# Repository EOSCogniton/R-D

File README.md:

# R-D Repository

Ce repository a été créé à l'occasion des stages d'applications de la Saison 2024, afin de permettre une conservation des connaissances acquises lors de ceux-ci. Il contient à ce jour les connaissances acquises sur la réalisation d'un VCU home-made.
Il est actuellement en cours de construction.

## Table of contents
1. VCU

## VCU
La partie VCU du repository contient le travail réalisé sur le VCU lors du stage FS@ECL de la Saison 2024. Lors de ce stage, un cahier des charges a été du VCU a été effectué ce qui a mené à un choix de micro-contrôleur sur lequel a été basé un banc de test.
Le cahier des charges est disponible directement dans le dossier "VCU", et les informations pertinentes par rapport au banc de test sont dans le dossier "VCU/Banc de test/"

### Banc de test du VCU basé sur le MCU ATSAMC21J18A-ANT
Description des différents documents présents dans le dossier "VCU/Banc de test/". Le travail a principalement été réalisé pour fournir des outils par rapport au test du code du VCU, en réalisant un banc de test à brancher à la carte de développement.

#### Dev_board_connector.png
Schéma des pins de la carte de développement ATSAMC21-XPro pour le MCU ATSAMC21J18.

#### Interface_Pins_Devboard.xlsx
Ce tableur est décomposé en deux feuilles : "PINS correspondance" et "références composants".*

Dans la feuille PINS correspondance, l'utilisation des différents pins utilisable par la carte de développement est détaillé.
Pour chaque pins de la carte, il est indiqué lesquels sont utilisés, à quelle pin du MCU ils sont reliés et à la fonctionnalité choisie pour le pin. Une description plus factuelle est aussi fournie avec des précisions sur l'utilisation du pin.

Dans la feuille "références composants", l'ensemble des composants utilisés pour la réalisation du pcb sont présents (hors résistances, condensateurs et connecteurs qui sont couramment utilisés dans l'écurie. Si besoin il est possible de retrouver les références sur le schematics KiCad). il sera notamment possible de trouver les références des régulateurs de tension linéaires, des LEDs, des potentiomètres, des switchs, des transceiver CAN et de la carte de développement ATSAMC21-XPro.

#### Schematics-banc
Schematics du pcb.

#### Code 
Exemple de code effectué sur MPLab X IDE pour mesurer un ADC.

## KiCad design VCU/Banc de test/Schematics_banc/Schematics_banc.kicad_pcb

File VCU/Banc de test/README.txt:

Banc de test du VCU ATSAMC21J18A-ANT

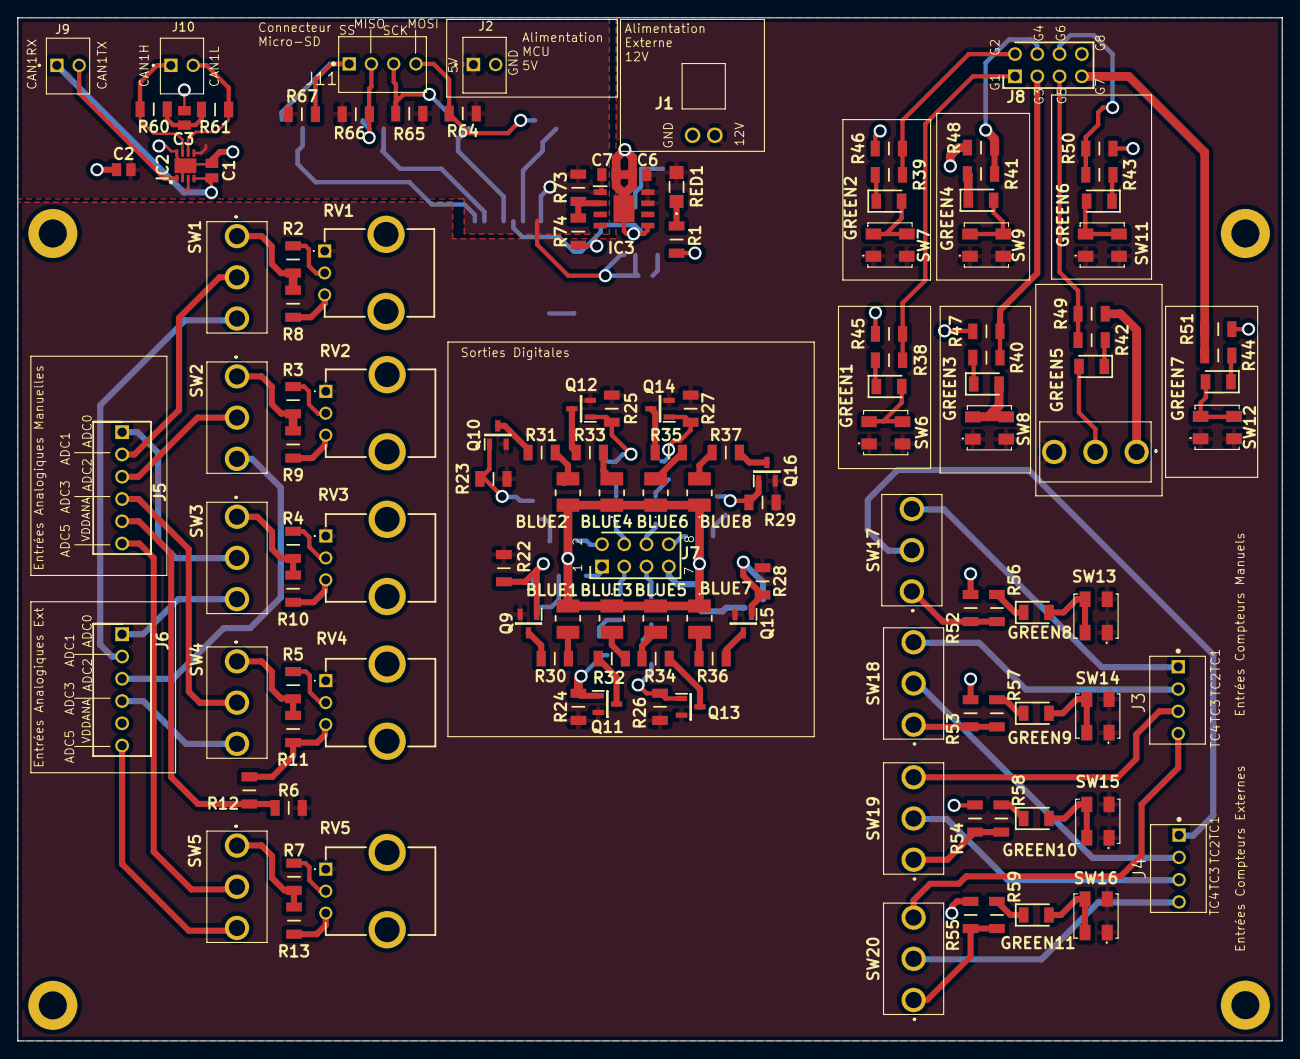
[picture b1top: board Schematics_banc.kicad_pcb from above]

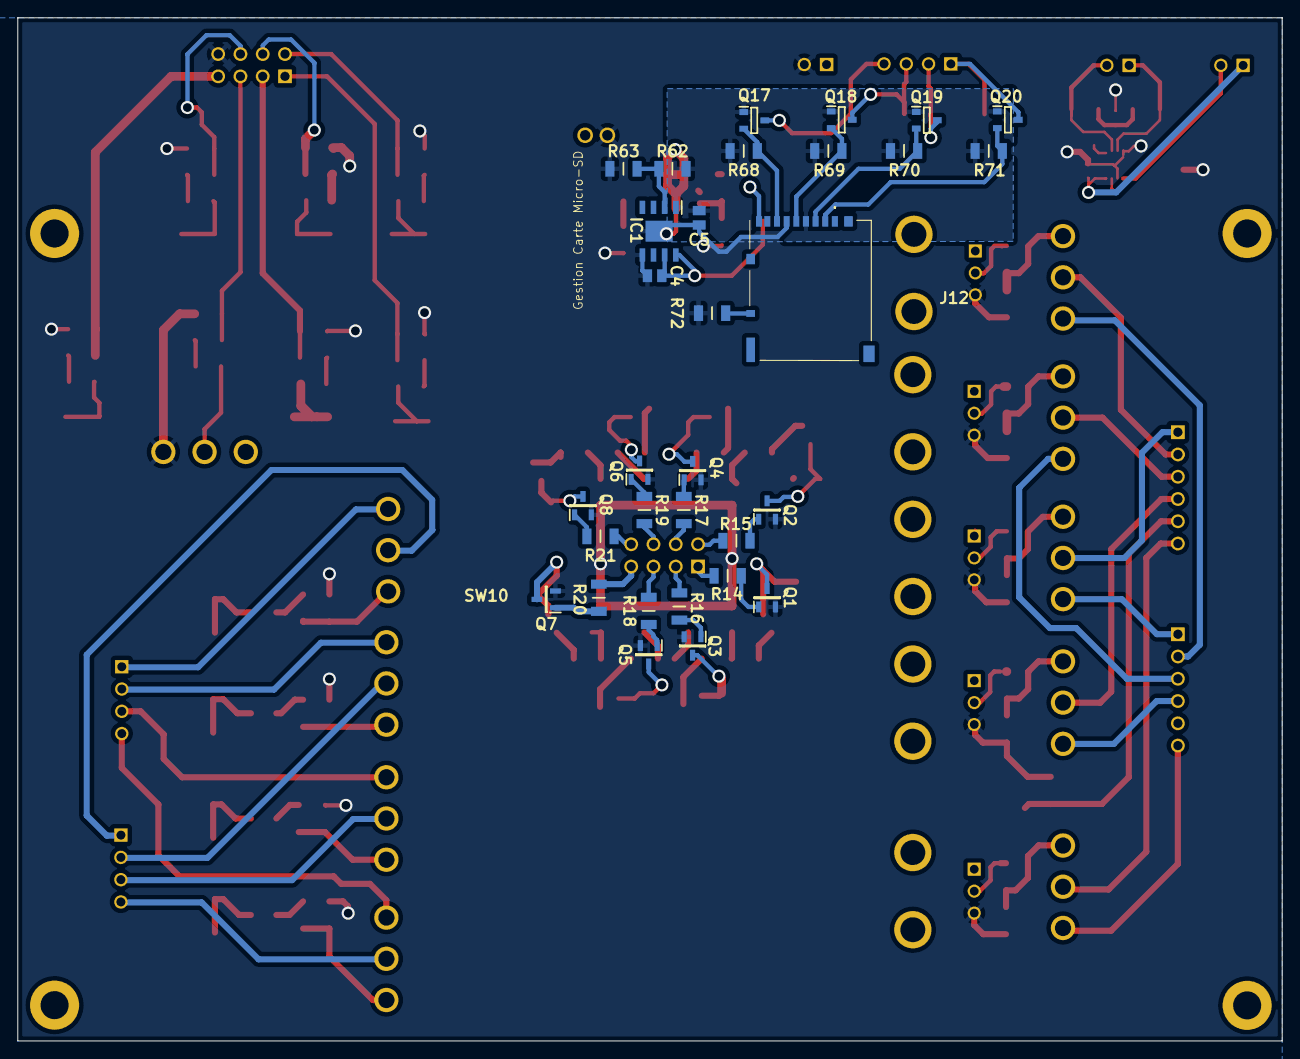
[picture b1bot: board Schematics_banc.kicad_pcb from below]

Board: 2 copper layers, 144.2 x 116.7 mm, 165 parts (31 on the bottom side), 123 nets.

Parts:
BLUE1, BLUE2, BLUE3, BLUE4, BLUE5, BLUE6, BLUE7, BLUE8: LB_T64G-V2CA-59-Z484; LBT64GV2CA59Z484
C1: 15p; CAPC2012X130N
C2: 100n; CAPC2012X130N
C3: 4.7u; CAPC2012X130N
C4, C7: 1u; CAPC2012X130N
C5, C6: 2.2u; CAPC2012X130N
GREEN1, GREEN2, GREEN3, GREEN4, GREEN5, GREEN6, GREEN7, GREEN8, GREEN9, GREEN10, GREEN11: VFJD1105W-5C63A-TR; LEDC3216X195N
IC1, IC3: TPS7B8633QDDARQ1; SOIC127P600X170-9N
IC2: ATA6561-GBQW-N; SON65P300X300X90-9N-D
J1: 2P Angle 171857-4002; 1718574002
J2, J9, J10: 2P Droit 2-11-2022; MOLEX_22-11-2022
J3, J4, J11: 4P Droit 22-11-2042; MOLEX_22-11-2042
J5, J6: 6P Droit 22-11-2062; HDRV6W87P0X254_1X6_1509X635X1092P
J7, J8: 10-97-7086; HDRV8W87P254_2X4_1016X508X1055P
J12: DM3AT-SF-PEJM5_40_; DM3ATSFPEJM540
M2, M2#2, M2#3, M2#4: MountingHole_3.2mm_M3_DIN965_Pad
Q1, Q2, Q3, Q4, Q5, Q6, Q7, Q8: MMBF170; SOT96P237X111-3N
Q9, Q10, Q11, Q12, Q13, Q14, Q15, Q16: SI2337DS-T1-BE3; SOT95P237X112-3N
Q17, Q18, Q19, Q20: BSS138; SOT95P240X120-3N
R1, R2, R3, R4, R5, R6, R7, R38, R39, R40, R41, R42, R43, R44, R52, R53, R54, R55: 21.5k; RESC3216X70N
R8, R9, R10, R11, R12, R13, R45, R46, R47, R48, R49, R50, R51, R56, R57, R58, R59: 11k; RESC3216X70N
R14, R15, R16, R17, R18, R19, R20, R21: 600; RESC3216X70N
R22, R23, R24, R25, R26, R27, R28, R29, R30, R31, R32, R33, R34, R35, R36, R37: 3k; RESC3216X70N
R60, R61, R72: 4.7k; RESC3216X70N
R62: 4k; RESC3216X70N
R63: 1k; RESC3216X70N
R64, R66, R67, R68, R70, R71: 20k; RESC3216X70N
R65, R69: 10k; RESC3216X70N
R73: 13.3k; RESC3216X70N
R74: 2k; RESC3216X70N
RED1: HSMC-C380; HSMCC380
RV1, RV2, RV3, RV4, RV5: R_Potentiometer; PTV09A4015UA503
SW1, SW2, SW3, SW4, SW5, SW10, SW17, SW18, SW19, SW20: 100SP1T1B4M2QE
SW6, SW7, SW8, SW9, SW11, SW12, SW13, SW14, SW15, SW16: 7914J-1-000E; 7914J1000E

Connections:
5V: C2.2, C4.2, C7.2, IC1.7 (EN), IC1.8 (IN), IC2.3 (VCC), IC2.5 (VIO), IC3.1 (OUT), J2.1, J12.CD1 (CARD_DETECT), R64.2, R65.2, R66.2, R67.2, R73.1
12V: C6.2, IC3.7 (EN), IC3.8 (IN), J1.1, Q9.2 (S), Q10.2 (S), Q11.2 (S), Q12.2 (S), Q13.2 (S), Q14.2 (S), Q15.2 (S), Q16.2 (S), R6.2, R22.1, R23.1, R24.1, R25.1, R26.1, R27.1, R28.1, R29.1, RED1.2 (A), RV1.1, RV2.1, RV3.1, RV4.1, RV5.1, SW6.1, SW6.2, SW7.1, SW7.2, SW8.1, SW8.2, SW9.1, SW9.2, SW10.3 (A), SW11.1, SW11.2, SW12.1, SW12.2, SW13.1, SW13.2, SW14.1, SW14.2, SW15.1, SW15.2, SW16.1, SW16.2
/Conversion 5V-3.3V/3.3V: C5.2, IC1.1 (OUT), J12.4 (VDD), Q17.1 (G), Q18.1 (G), Q19.1 (G), Q20.1 (G), R62.2, R68.2, R69.2, R70.2, R71.2
/Conversion 5V-3.3V/MISO_3.3V: J12.3 (CMD), Q19.2 (S), R70.1
/Conversion 5V-3.3V/MOSI_3.3V: J12.7 (DAT0), Q17.2 (S), R68.1
/Conversion 5V-3.3V/SCK_3.3V: J12.5 (CLK), Q18.2 (S), R69.1
/Conversion 5V-3.3V/SS_3.3V: J12.2 (CD/DAT3), Q20.2 (S), R71.1
ADC5: J5.6, SW5.2 (B)
ADC5_EXT: J6.6, SW5.3 (A)
AIR+_cmd: J7.1, R14.1
AIR+_st: J8.1, R38.1, R45.2
AIR-_cmd: J7.2, R15.1
AIR-_st: J8.2, R39.1, R46.2
APPS1: J5.2, SW1.2 (B)
APPS1_EXT: J6.2, SW1.3 (A)
APPS2: J5.3, SW2.2 (B)
APPS2_EXT: J6.3, SW2.3 (A)
BrakeLight_cmd: J7.3, R16.1
BuzzerR2D_cmd: J7.4, R17.1
CAN1H: IC2.7 (CANH), J10.1, R60.2
CAN1L: IC2.6 (CANL), J10.2, R61.1
CAN1RX: C1.2, IC2.4 (RXD), J9.1
CAN1TX: IC2.1 (TXD), J9.2
Decharge_cmd: J7.6, R19.1
Dry/WetSwitch_st: J8.5, R42.2, R49.2
FBPS: J5.1, SW3.2 (B)
FBPS_EXT: J6.1, SW3.3 (A)
FLWSS_in: J4.2, SW18.2 (B)
FLWSS_out: J3.2, SW18.3 (A)
FRWSS_in: J4.1, SW17.2 (B)
FRWSS_out: J3.1, SW17.3 (A)
GND: BLUE1.1 (K), BLUE2.1 (K), BLUE3.1 (K), BLUE4.1 (K), BLUE5.1 (K), BLUE6.1 (K), BLUE7.1 (K), BLUE8.1 (K), C1.1, C2.1, C3.1, C4.1, C5.1, C6.1, C7.1, IC1.5 (GND_1), IC1.9 (GND_2), IC2.2 (GND), IC2.8 (STBY), IC2.9 (EP), IC3.5 (GND_1), IC3.9 (GND_2), J1.2, J2.2, J8.8, J12.6 (VSS), Q1.2 (S), Q2.2 (S), Q3.2 (S), Q4.2 (S), Q5.2 (S), Q6.2 (S), Q7.2 (S), Q8.2 (S), R1.1, R8.2, R9.2, R10.2, R11.2, R12.2, R13.2, R45.1, R46.1, R47.1, R48.1, R49.1, R50.1, R51.1, R56.1, R57.1, R58.1, R59.1, R63.2, R72.2, R74.2, RV1.3, RV2.3, RV3.3, RV4.3, RV5.3, SW10.1 (C)
GPIO1: J7.7, R20.1
GPIO2: J8.6, R43.1, R50.2
GPIO3: J7.8, R21.1
GPIO4: J8.7, R44.1, R51.2
LV_BATT: J5.5, R6.1, R12.1
MISO_5V: J11.2, Q19.3 (D), R66.1
MOSI_5V: J11.4, Q17.3 (D), R64.1
unnamed: BLUE1.2 (A), R30.2
unnamed: BLUE2.2 (A), R31.2
unnamed: BLUE3.2 (A), R32.2
unnamed: BLUE4.2 (A), R33.2
unnamed: BLUE5.2 (A), R34.2
unnamed: BLUE6.2 (A), R35.2
unnamed: BLUE7.2 (A), R36.2
unnamed: BLUE8.2 (A), R37.2
unnamed: C3.2, R60.1, R61.2
unnamed: GREEN1.2 (A), SW6.3 (K), SW6.4 (A)
unnamed: GREEN1.1 (K), R38.2
unnamed: GREEN2.2 (A), SW7.3 (K), SW7.4 (A)
unnamed: GREEN2.1 (K), R39.2
unnamed: GREEN3.2 (A), SW8.3 (K), SW8.4 (A)
unnamed: GREEN3.1 (K), R40.2
unnamed: GREEN4.2 (A), SW9.3 (K), SW9.4 (A)
unnamed: GREEN4.1 (K), R41.2
unnamed: GREEN5.2 (A), SW10.2 (B)
unnamed: GREEN5.1 (K), R42.1
unnamed: GREEN6.2 (A), SW11.3 (K), SW11.4 (A)
unnamed: GREEN6.1 (K), R43.2
unnamed: GREEN7.2 (A), SW12.3 (K), SW12.4 (A)
unnamed: GREEN7.1 (K), R44.2
unnamed: GREEN8.2 (A), SW13.3 (K), SW13.4 (A)
unnamed: GREEN8.1 (K), R52.2
unnamed: GREEN9.2 (A), SW14.3 (K), SW14.4 (A)
unnamed: GREEN9.1 (K), R53.2
unnamed: GREEN10.2 (A), SW15.3 (K), SW15.4 (A)
unnamed: GREEN10.1 (K), R54.2
unnamed: GREEN11.2 (A), SW16.3 (K), SW16.4 (A)
unnamed: GREEN11.1 (K), R55.2
unnamed: IC1.2 (FB/NC), R62.1, R63.1
unnamed: IC3.2 (FB/NC), R73.2, R74.1
unnamed: Q1.3 (D), Q9.1 (G), R22.2
unnamed: Q1.1 (G), R14.2
unnamed: Q2.1 (G), R15.2
unnamed: Q3.1 (G), R16.2
unnamed: Q4.1 (G), R17.2
unnamed: Q5.1 (G), R18.2
unnamed: Q6.1 (G), R19.2
unnamed: Q7.1 (G), R20.2
unnamed: Q8.1 (G), R21.2
unnamed: Q9.3 (D), R30.1
unnamed: Q10.3 (D), R31.1
unnamed: Q2.3 (D), Q10.1 (G), R23.2
unnamed: Q11.3 (D), R32.1
unnamed: Q3.3 (D), Q11.1 (G), R24.2
unnamed: Q12.3 (D), R33.1
unnamed: Q4.3 (D), Q12.1 (G), R25.2
unnamed: Q13.3 (D), R34.1
unnamed: Q5.3 (D), Q13.1 (G), R26.2
unnamed: Q14.3 (D), R35.1
unnamed: Q6.3 (D), Q14.1 (G), R27.2
unnamed: Q15.3 (D), R36.1
unnamed: Q7.3 (D), Q15.1 (G), R28.2
unnamed: Q16.3 (D), R37.1
unnamed: Q8.3 (D), Q16.1 (G), R29.2
unnamed: R2.2, RV1.2
unnamed: R3.2, RV2.2
unnamed: R4.2, RV3.2
unnamed: R5.2, RV4.2
unnamed: R7.2, RV5.2
unnamed: R1.2, RED1.1 (K)
unnamed: R2.1, R8.1, SW1.1 (C)
unnamed: R3.1, R9.1, SW2.1 (C)
unnamed: R4.1, R10.1, SW3.1 (C)
unnamed: R5.1, R11.1, SW4.1 (C)
unnamed: R7.1, R13.1, SW5.1 (C)
unnamed: R52.1, R56.2, SW17.1 (C)
unnamed: R53.1, R57.2, SW18.1 (C)
unnamed: R54.1, R58.2, SW19.1 (C)
unnamed: R55.1, R59.2, SW20.1 (C)
Precharge_cmd: J7.5, R18.1
R2D_Button: J8.4, R41.1, R48.2
RBPS: J5.4, SW4.2 (B)
RBPS_EXT: J6.4, SW4.3 (A)
RLWSS_in: J4.4, SW20.2 (B)
RLWSS_out: J3.4, SW20.3 (A)
RRWSS_in: J4.3, SW19.2 (B)
RRWSS_out: J3.3, SW19.3 (A)
SCK_5V: J11.3, Q18.3 (D), R65.1
SD_INSERT: J12.MP3, R72.1
SS_SDC_5V: J11.1, Q20.3 (D), R67.1
TSON_Button: J8.3, R40.1, R47.2

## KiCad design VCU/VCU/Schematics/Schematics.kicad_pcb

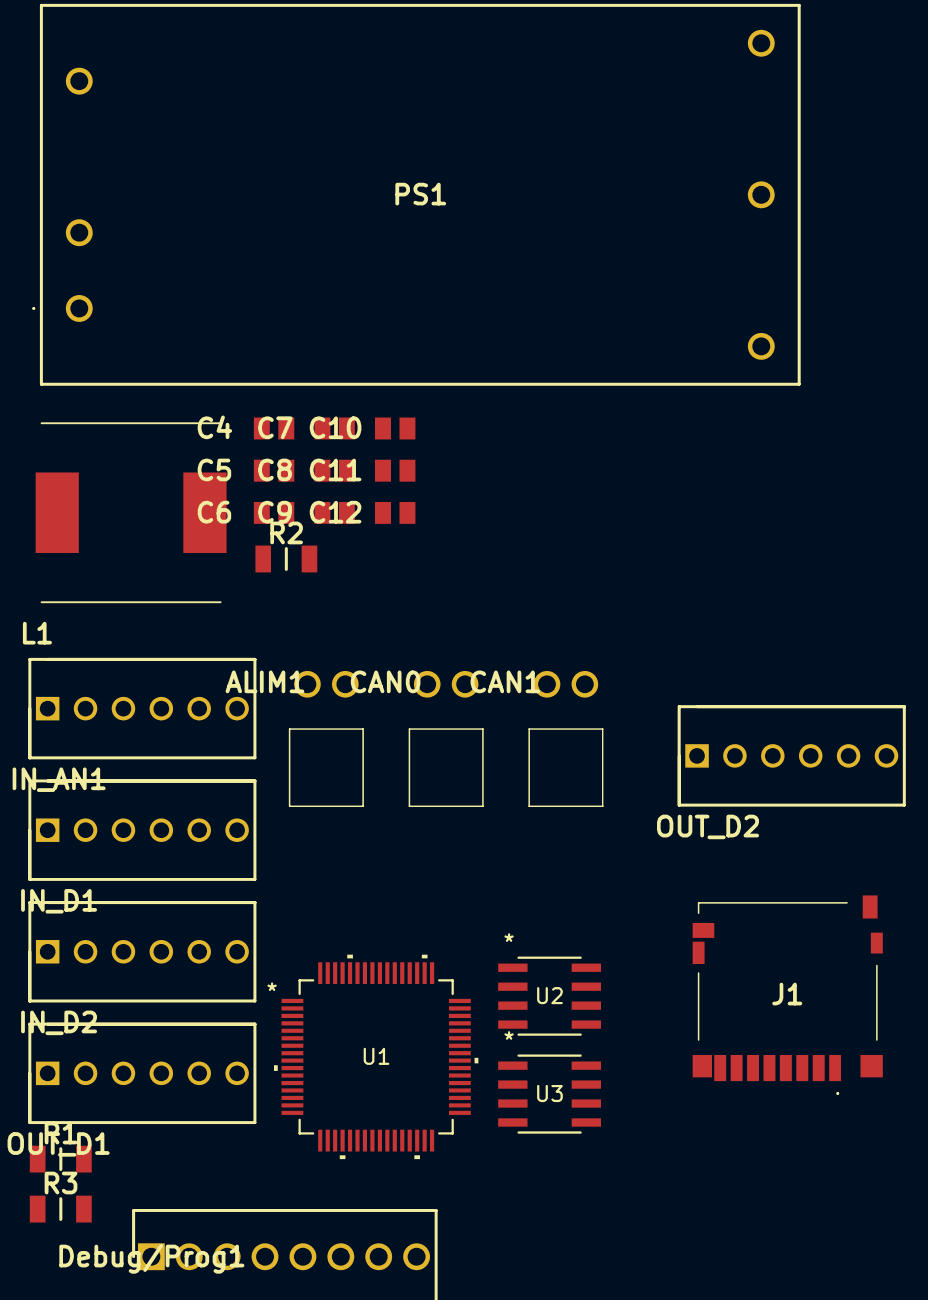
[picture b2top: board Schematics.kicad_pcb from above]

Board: 2 copper layers, 27 parts (0 on the bottom side), 16 nets, no tracks yet.

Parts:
ALIM1: 2P Angle 171857-4002; 1718574002
C4, C6, C7, C9, C12: 100n; CAPC2012X130N
C5, C8: 10u; CAPC2012X130N
C10: 1u; CAPC2012X130N
C11: 22u; CAPC2012X130N
CAN0, CAN1: 2P Angle 171857-4002; 1718574002
Debug/Prog1: 171856-1008; SHDR8W99P0X254_1X8_2017X635X1124P
IN_AN1: 6P Droit 22-11-2062; HDRV6W87P0X254_1X6_1509X635X1092P
IN_D1, IN_D2: 6P Droit 22-11-2062; HDRV6W87P0X254_1X6_1509X635X1092P
J1: DM3D-SF; DM3DSF
L1: 10u; WE-PD_1260_1245_1280_121054
OUT_D1, OUT_D2: 6P Droit 22-11-2062; HDRV6W87P0X254_1X6_1509X635X1092P
PS1: TEN_40-1211E; TEN401211E
R1, R3: 120; RESC3216X70N
R2: 20k; RESC3216X70N
U1: ATSAMC21J18A-ANT; TQFP64_10x10MC_MCH
U2, U3: ATA6561-GAQW-N; SOIC8_4P9X3P9MC_MCH

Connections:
CAN0_H: CAN0.1, R1.2, U2.7 (CANH)
CAN0_L: CAN0.2, R1.1, U2.6 (CANL)
CAN1_H: CAN1.1, R3.2, U3.7 (CANH)
CAN1_L: CAN1.2, R3.1, U3.6 (CANL)
GND: ALIM1.2, C4.1, C5.1, C6.1, C7.1, C8.1, C9.1, C10.1, C11.1, C12.1, Debug/Prog1.3, PS1.2 (-VIN_(GND)), U1.7 (GNDANA), U1.22 (GND), U1.33 (GND), U1.47 (GND), U1.54 (GND), U2.2 (GND), U3.2 (GND)
LV_ALIM: ALIM1.1, PS1.1 (+VIN_(VCC)), PS1.3 (REMOTE_ON/OFF)
unnamed: PS1.5 (-VOUT), R2.1
unnamed: PS1.6 (TRIM), R2.2
RESETN: Debug/Prog1.1, U1.52 (RESETN)
RX_CAN0: U1.46 (PA25), U2.4 (RXD)
SWDCLK: Debug/Prog1.5, U1.57 (PA30)
SWDIO: Debug/Prog1.8, U1.58 (PA31)
TX_CAN0: U1.45 (PA24), U2.1 (TXD)
VDD_ANA: C4.2, C5.2, L1.2, U1.8 (VDDANA)
VDD_CORE: C9.2, C10.2, U1.55 (VDDCORE)
VDD_IO: C6.2, C7.2, C8.2, C11.2, C12.2, Debug/Prog1.2, L1.1, PS1.4 (+VOUT), U1.34 (VDDIO), U1.48 (VDDIO), U1.56 (VDDIN), U2.3 (VCC), U2.5 (VIO), U3.3 (VCC), U3.5 (VIO)

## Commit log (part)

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2024-06-07 Ajout CdC VCU et gitignore
    Ajout du Cahier des Charges du VCU et du gitignore pour les fichiers KiCad inutiles
2024-06-10 Test import de composant librairie
    Import du composant VCU et test si l'importation fonctionne sur plusieurs PC
2024-06-10 Update schematics
    Ajout de la transmission CAN et du schéma d'alimentation du VCU
2024-06-11 Update schematics
    Update du schema avec ajout des embases et wiring de l'alimentation
2024-06-12 Update schematics VCU et ajout protocoles de tests
    Ajout de protocoles de tests et ajout de l'interface microSD dans les schematics
2024-06-13 Ajout readME et Update schematics
2024-06-14 Update interface pins dev board
2024-06-21 Adding sguerel files
2024-06-24 Des modifs qui marchent?
2024-06-26 Modifs sur le modèle de Bhrol
2024-06-28 Finalisation Schematics VCU Dev_Bench et tests codes
    Finalisation des schematics pour le banc de test et de developpement du VCU, et ajout des premiers tests de code sur MPLAB effectués sur Dev board.
2024-07-04 Update schematic
2024-07-05 Routage Support de programmation VCU
2024-07-10 Routage Final
2024-07-22 Modèle 6 et plans manip
2024-07-26 Fin de stage
2024-07-26 Dernières modifs, fin de stage
2025-05-16 Organisation et ajout modèles v1
2025-05-23 Nouveau modèle
2025-06-06 Ajout CAO démonstrateur
2025-06-10 maj nouveaux modèles
2025-07-20 Ajout rapport de stage VCU
    Ajout du rapport de stage effectué sur le VCU lors de l'été 2024.
2025-10-27 Update TV et TC
2025-10-27 Modèle véhicule updaté
2026-03-14 Ajout torque structure
2026-03-15 Ajout FF
2026-05-26 création stage aero + doc
2026-05-28 plus d'accent
2026-05-28 suppression du dossier pack aero
2026-05-28 reajout dossier pack
2026-05-28 suppression fichier
2026-05-28 ajout doc + optimumlab
2026-05-29 ajout doc
2026-06-03 doc aero
2026-06-05 Update VCU, R2D protocol, CAN communication, TS Activation
2026-06-22 Minor modifications to car model (backup)
2026-06-22 Tire Model Update
2026-06-25 Upgrades backup
2026-06-25 Added tire model v3 and updated car model
2026-06-27 Launch Start
2026-06-27 Launch start backup
2026-06-30 Launch start completed + Vx Kalman estimator + TC/TV validated
2026-06-30 Latest updates
